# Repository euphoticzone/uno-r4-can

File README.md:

# uno-r4-can

A prototype shield that provides an isolated CAN transceiver for use with the Arduino Uno R4 Wifi or Minima.

The jumper selects between the diffent pins used for CAN on the Minima and Wifi versions.

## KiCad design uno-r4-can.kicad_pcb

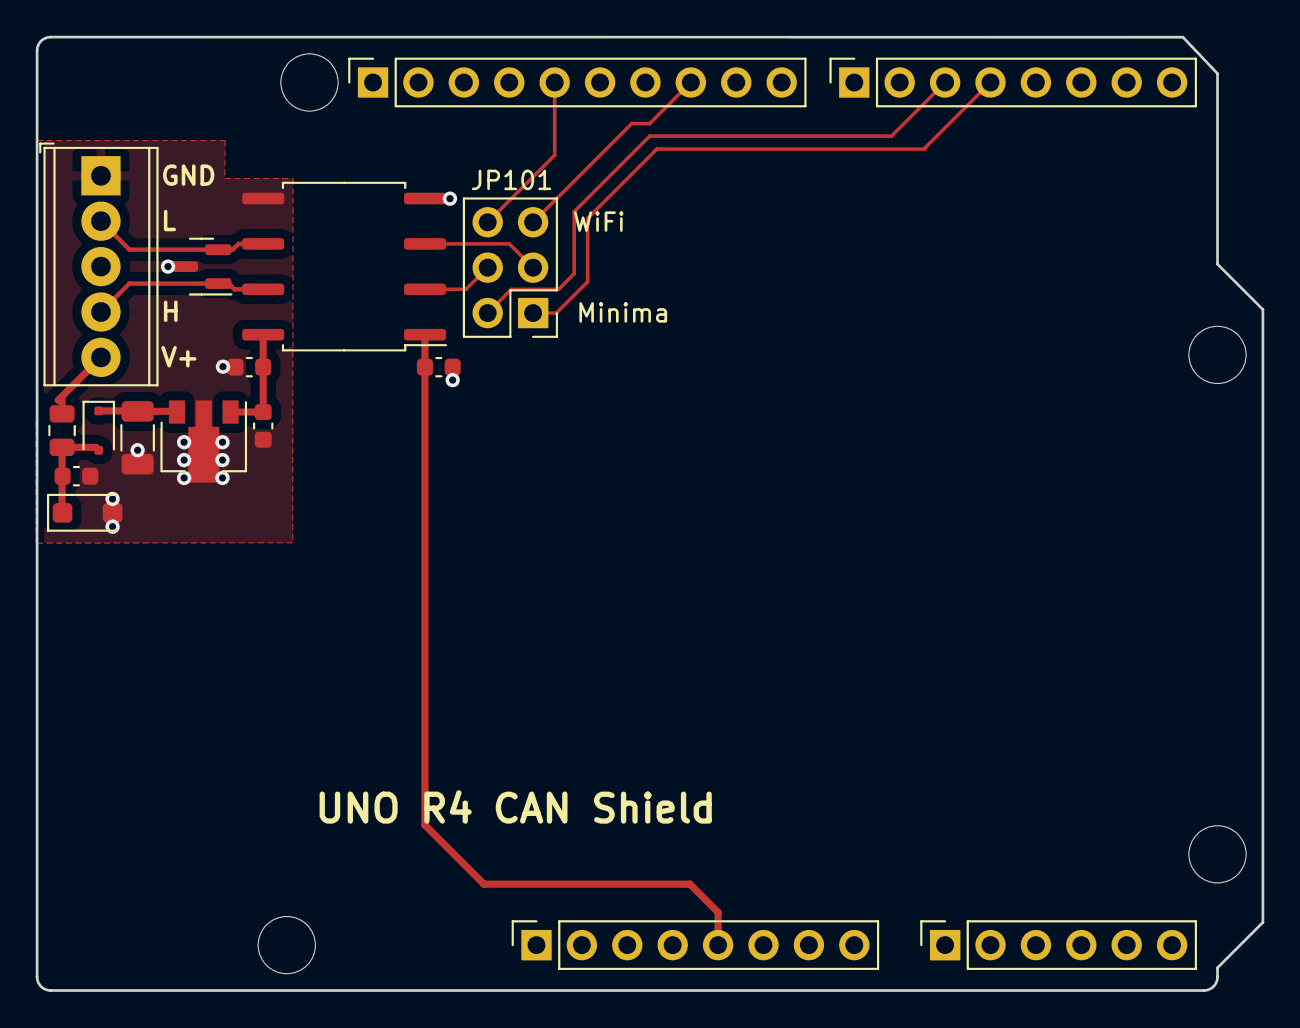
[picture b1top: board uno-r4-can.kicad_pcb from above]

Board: 2 copper layers, 68.6 x 53.3 mm, 21 parts (0 on the bottom side), 15 nets.

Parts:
C101: 10nF 50V; C_0603_1608Metric
C102: 1µF 50V; C_1206_3216Metric
C103, C104, C105: 100nF; C_0603_1608Metric
D101: SMF30CA; D_SOD-123F
D102: 1N5819WS; D_SOD-323F
D103: PESD2CAN; SOT-23
F101: 2.5A; Fuse_0805_2012Metric
J101: CANOpen; TerminalBlock_Phoenix_MPT-0,5-5-2.54_1x05_P2.54mm_Horizontal
J102: Power; PinSocket_1x08_P2.54mm_Vertical
J103: Analog; PinSocket_1x06_P2.54mm_Vertical
J104: Digital/PWM; PinSocket_1x10_P2.54mm_Vertical
J105: Digital/PWM; PinSocket_1x08_P2.54mm_Vertical
JP101: Minima/WiFi; PinHeader_2x03_P2.54mm_Vertical
MH1, MH2, MH3, MH4: MountingHole_3.2mm
U101: L78L05_SOT89; SOT-89-3
U102: ISO1050DUB; SOP-8_6.62x9.15mm_P2.54mm

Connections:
+5V: C105.2, J102.5, U102.1 (VCC1)
/4: J105.4, JP101.1
/13: J104.5, JP101.6
/CAN_H: D103.1 (K), J101.4 (CAN_H), U102.7 (CANH)
/CAN_L: D103.2 (K), J101.2 (CAN_L), U102.6 (CANL)
/CAN_RX: JP101.4, U102.2 (RXD)
/CAN_TX: JP101.3, U102.3 (TXD)
/CAN_V+: F101.2, J101.5 (CAN_V+)
/CAN_V_{PROT}: C101.1, D101.1 (A1), D102.2 (A), F101.1
/~5: J105.3, JP101.2
/~10: J104.8, JP101.5
GND: C105.1, J102.6, J102.7, J104.4, U102.4 (GND1)
GNDCAN: C101.2, C102.2, C103.2, C104.2, D101.2 (A2), D103.3 (A), J101.1 (CAN_GND), U101.2 (GND), U102.5 (GND2)
unnamed: C102.1, D102.1 (K), U101.3 (IN)
VCAN: C103.1, C104.1, U101.1 (OUT), U102.8 (VCC2)

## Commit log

2023-10-29 Init
2023-10-31 Prototype assembled by JLCPCB
2023-11-01 Printable docs for schematic and model
2023-11-01 Add README.md
2023-11-11 Wifi TX is on pin 10
